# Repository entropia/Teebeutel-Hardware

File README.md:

# Teebeutel

An (experimental) ESP32-dev-board in the shape of the Entropia logo.

Head over to the [wiki](https://gitlab.jadyn.dev/jadyn/Teebeutel/-/wikis/home) for more information.

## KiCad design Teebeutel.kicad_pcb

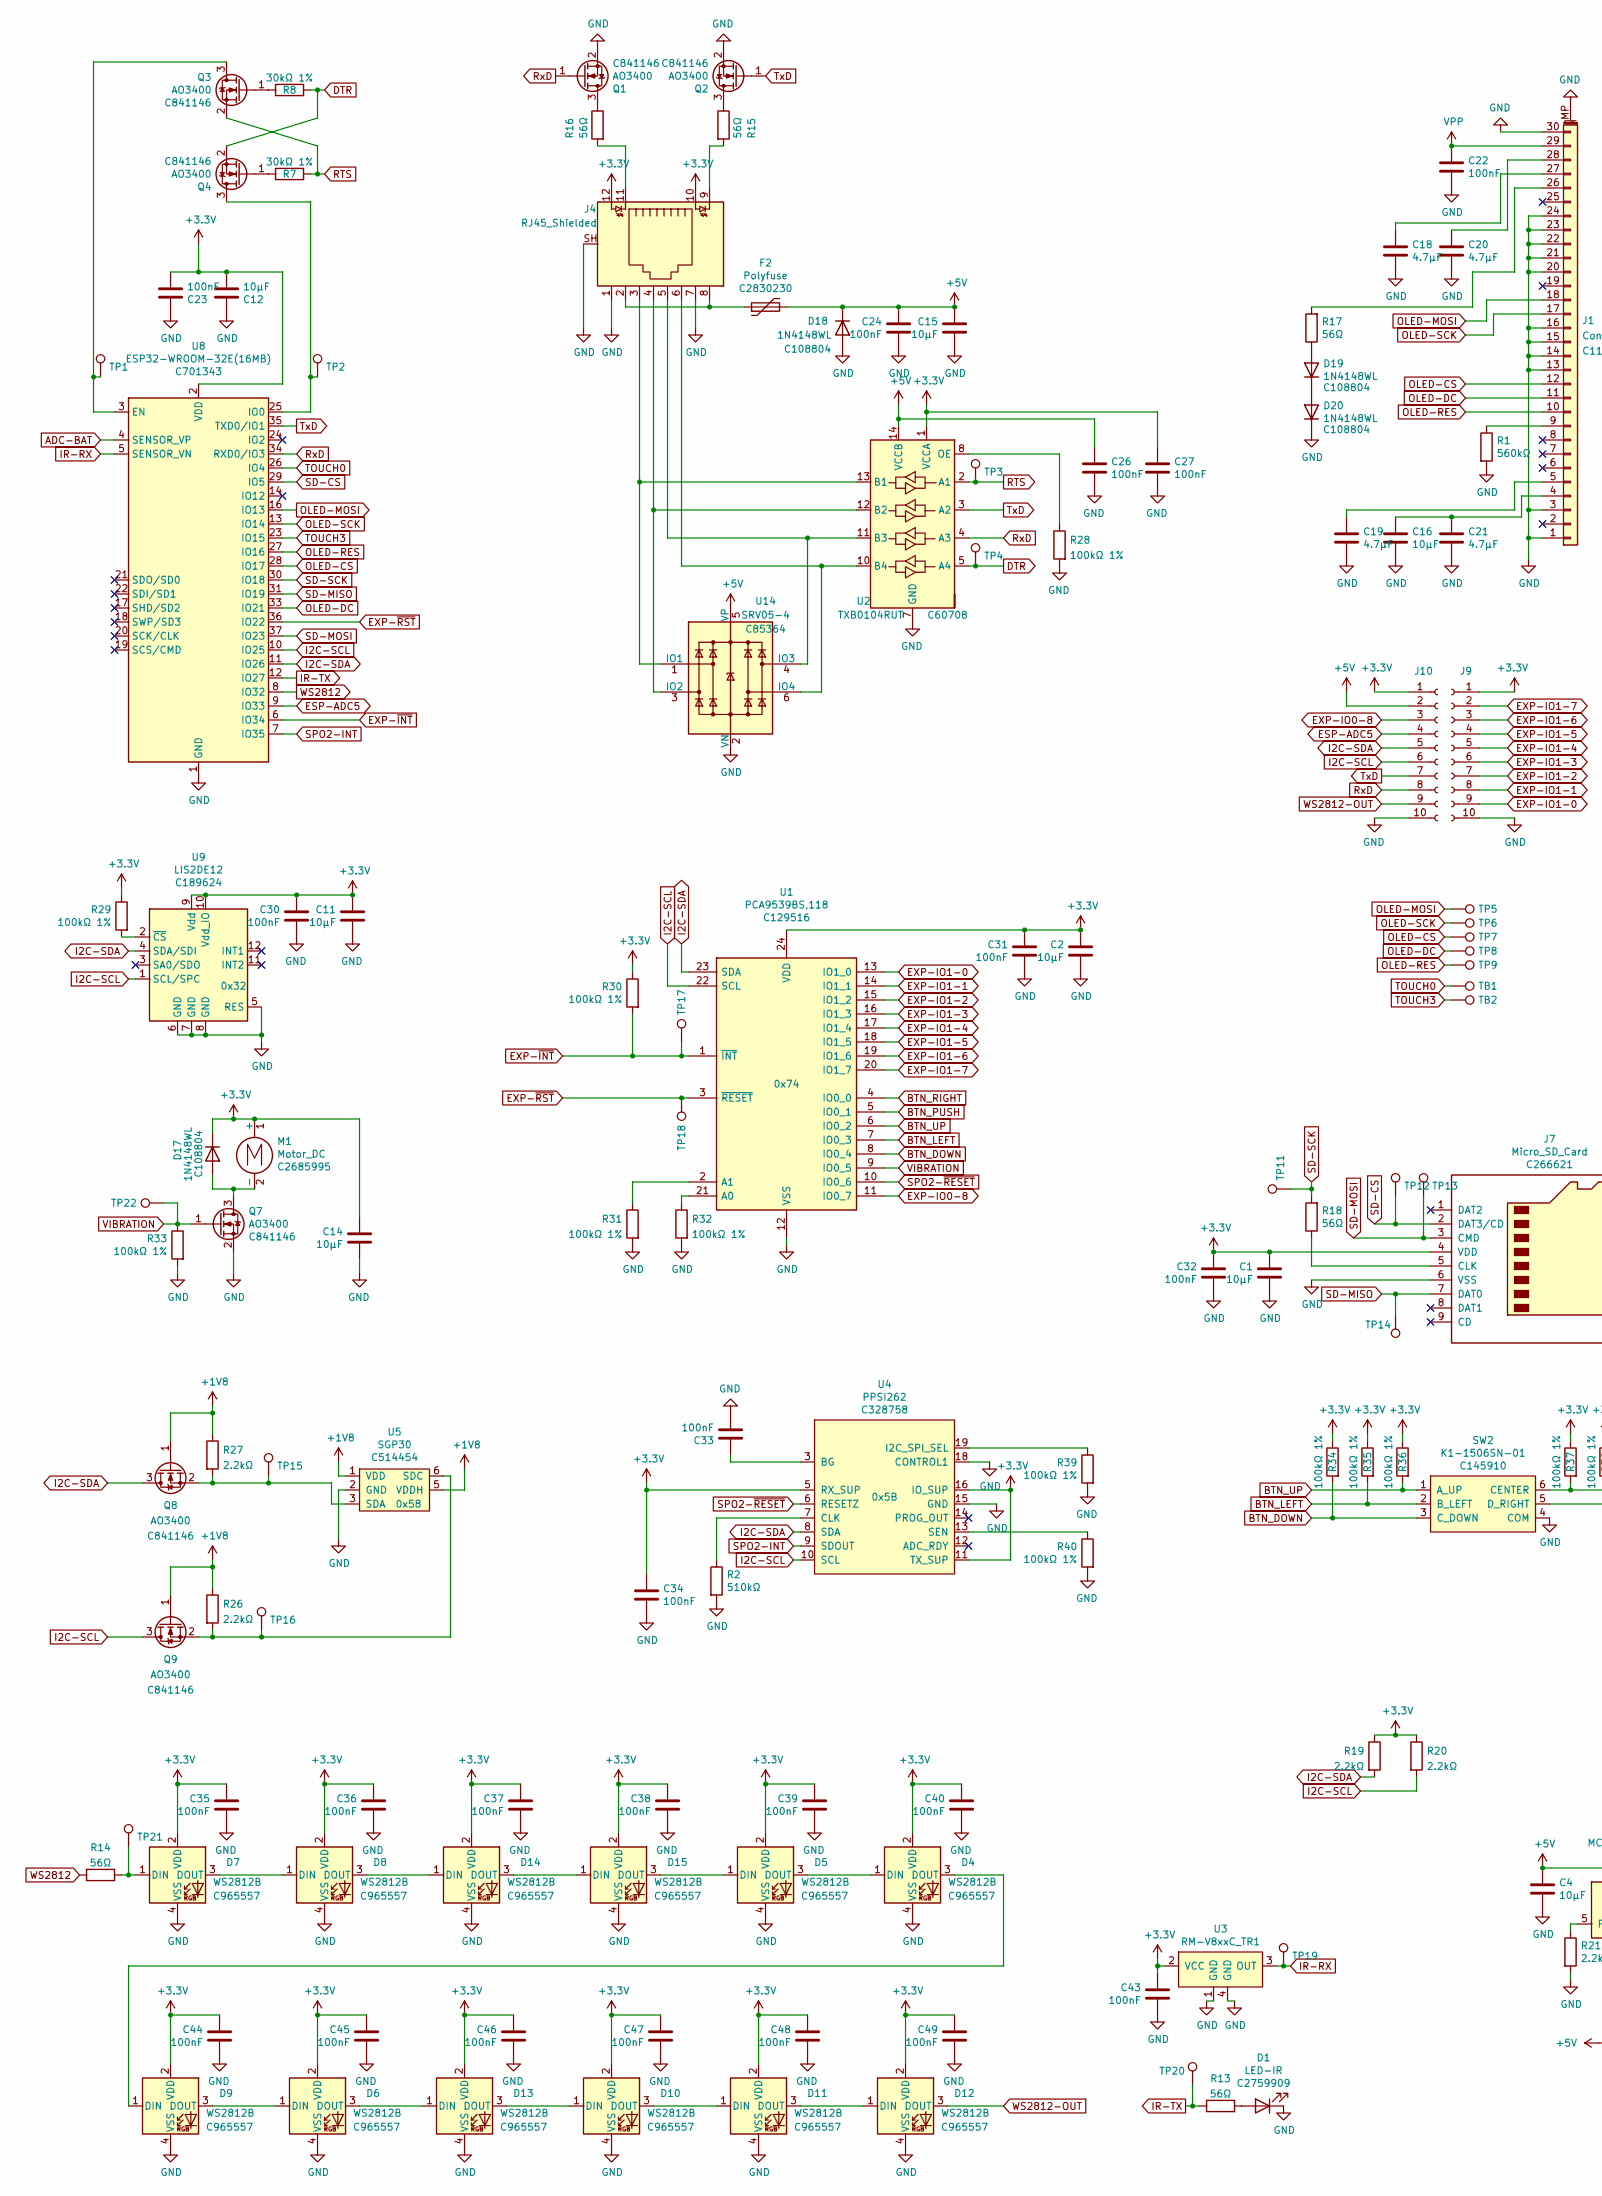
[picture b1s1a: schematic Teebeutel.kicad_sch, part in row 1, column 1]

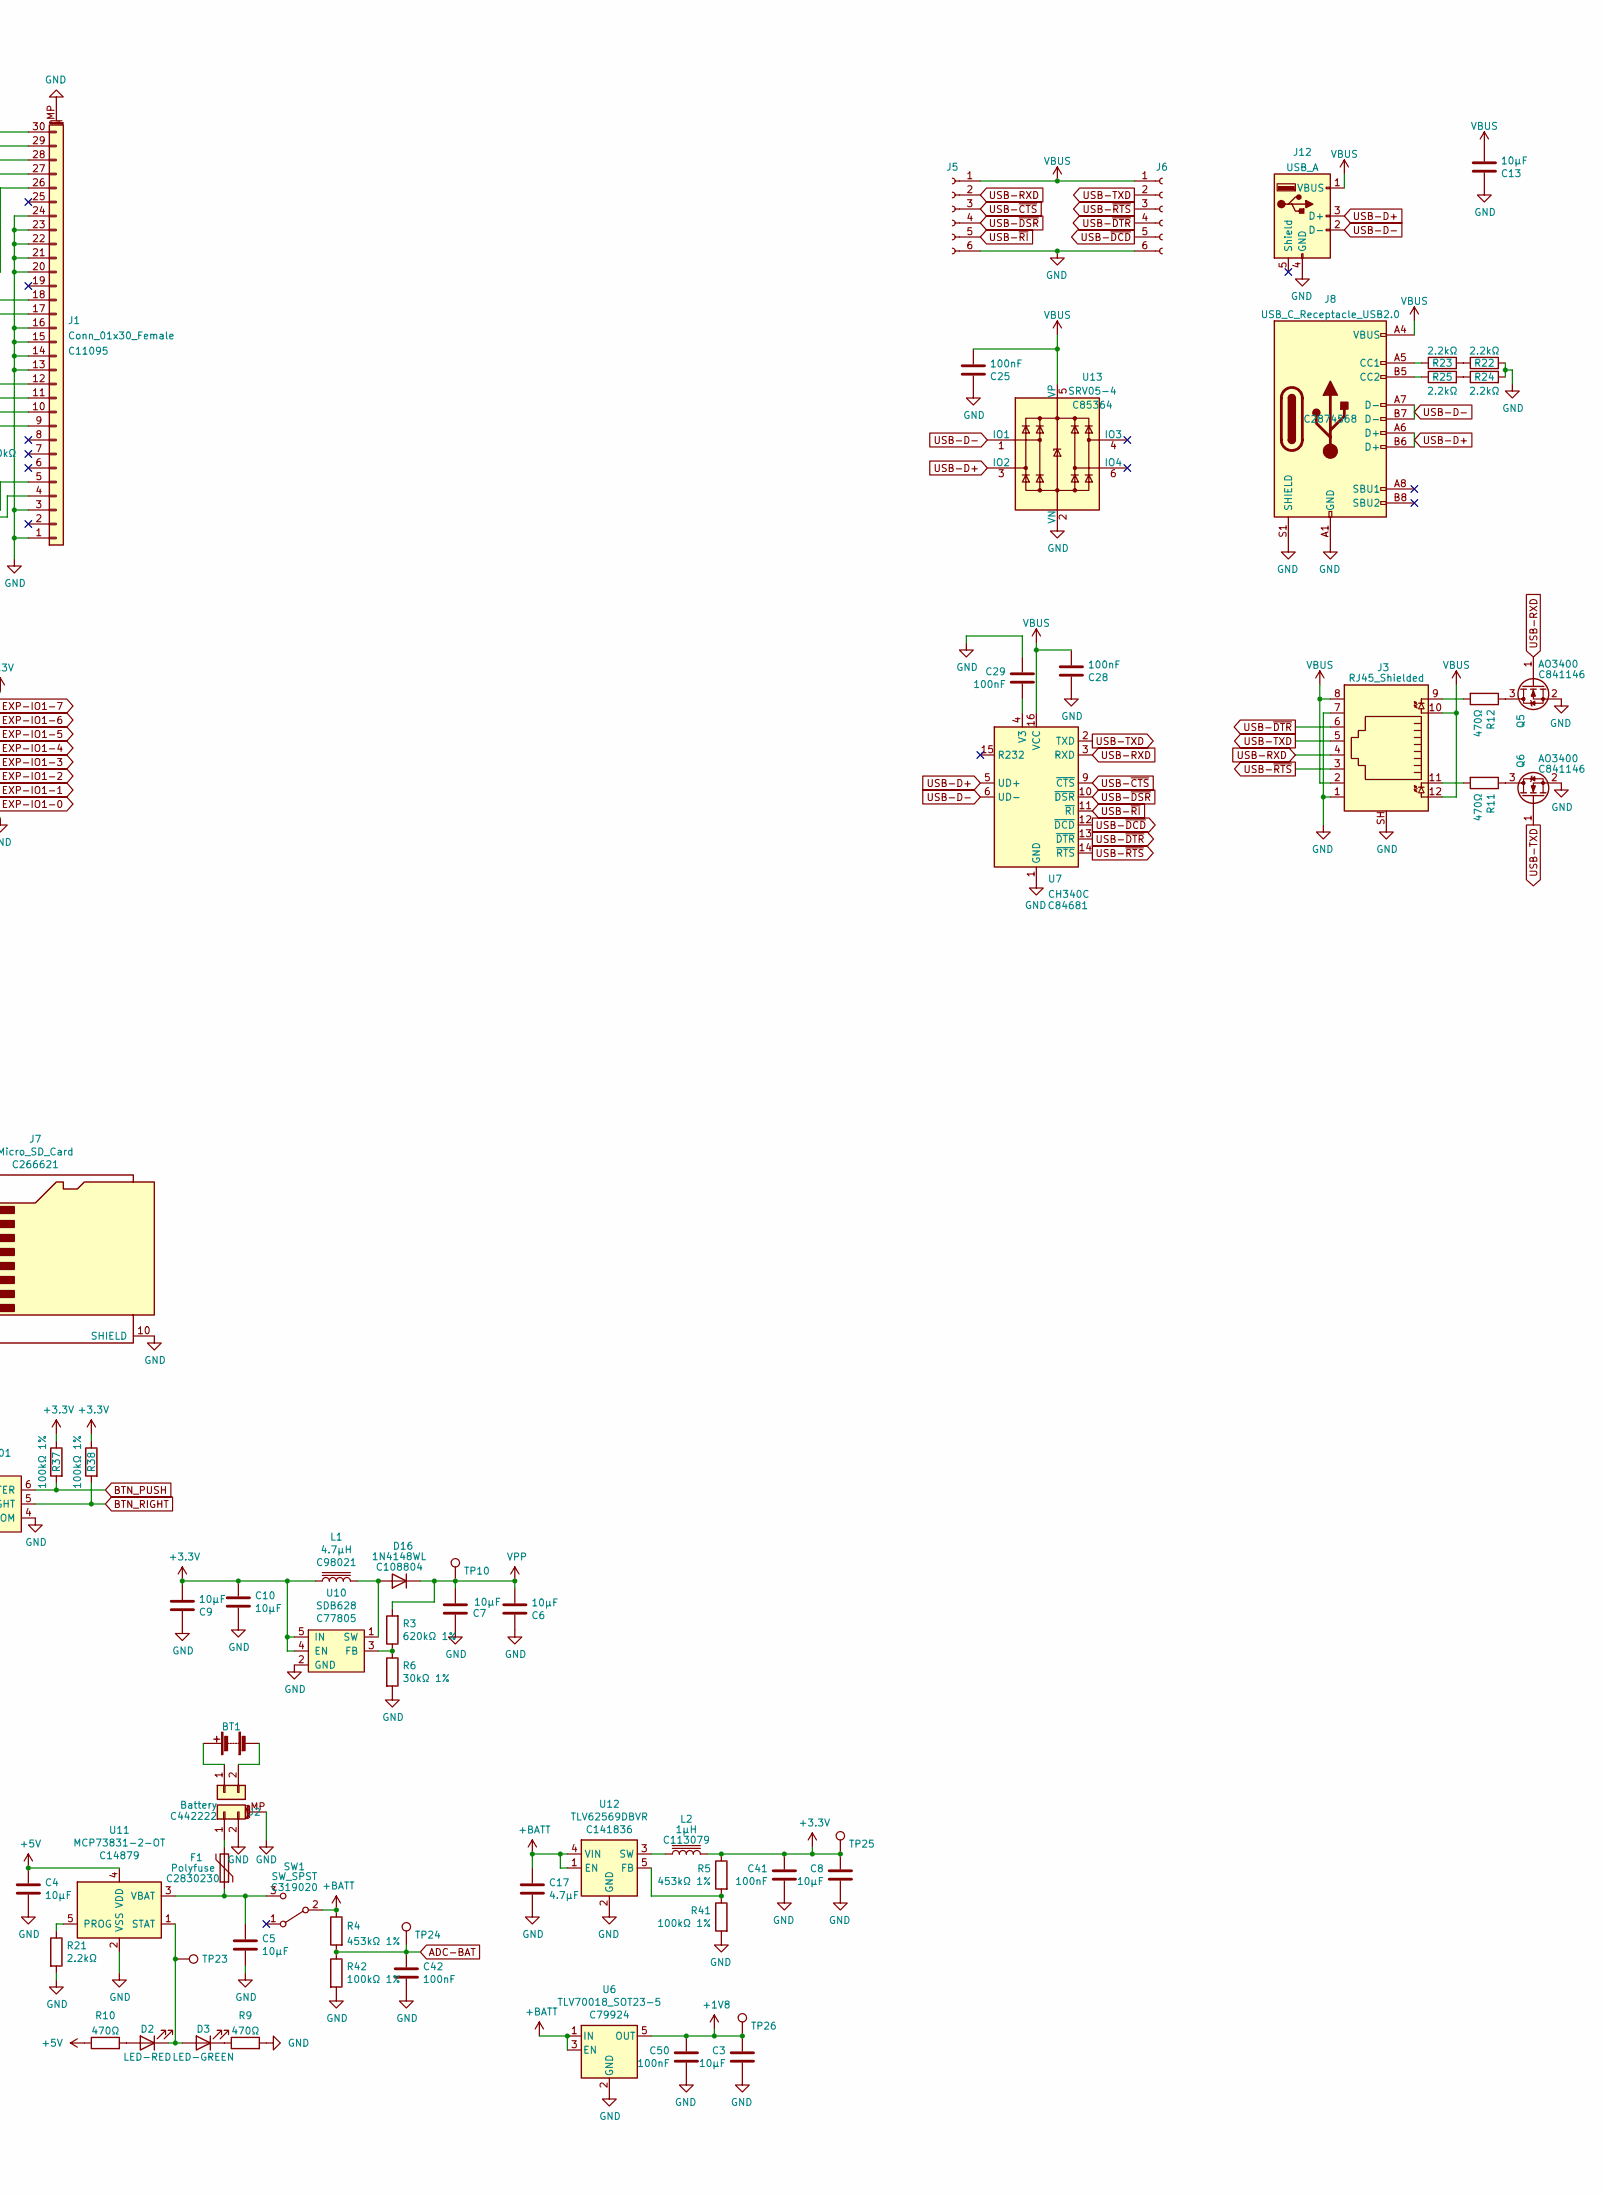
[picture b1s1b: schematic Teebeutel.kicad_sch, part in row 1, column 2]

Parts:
BT1: Battery
C1, C2, C3, C4, C5, C6, C7, C8, C9, C10, C11, C12, C13, C14, C15, C16: 10µF; C_0603_1608Metric; LCSC C19702
C17, C18, C19, C20, C21: 4.7µF; C_0603_1608Metric; LCSC C19666
C22, C23, C24, C25, C26, C27, C28, C29, C30, C31, C32, C33, C34, C35, C36, C37, C38, C39, C40, C41, C42, C43, C44, C45, C46, C47, C48, C49, C50: 100nF; C_0603_1608Metric; LCSC C14663
D1: LED-IR; LKIR30102C; LCSC C2759909
D2: LED-RED; LED_0805_2012Metric; LCSC C84256
D3: LED-GREEN; LED_0805_2012Metric; LCSC C84257
D4, D5, D6, D7, D8, D9, D10, D11, D12, D13, D14, D15: WS2812B; WS2812B-4020; LCSC C965557
D16, D17, D18, D19, D20: 1N4148WL; D_SOD-123F; LCSC C108804
F1, F2: Polyfuse; Fuse_0805_2012Metric; LCSC C2830230
J1: Conn_01x30_Female; TE_3-1734839-0_1x30-1MP_P0.5mm_Horizontal; LCSC C11095
J2: Battery; JST_PH_S2B-PH-SM4-TB_1x02-1MP_P2.00mm_Horizontal; LCSC C442222
J3, J4: RJ45_Shielded; RJ45_Amphenol_RJHSE538X; LCSC C464587
J5: Conn_01x06_Female; PinSocket_1x06_P2.54mm_Vertical_SMD_Pin1Right; MOUSER 801-83-006-30-001101
J6: Conn_01x06_Female; PinSocket_1x06_P2.54mm_Vertical_SMD_Pin1Left; MOUSER 801-83-006-30-001101
J7: Micro_SD_Card; TF15X15; LCSC C266621
J8: USB_C_Receptacle_USB2.0; USB_C_Receptacle_Palconn_UTC16-G; LCSC C2874568
J9: Conn_01x10_Female; PinSocket_1x10_P2.54mm_Vertical_SMD_Pin1Left; MOUSER 437-8018301030001101
J10: Conn_01x10_Female; PinSocket_1x10_P2.54mm_Vertical_SMD_Pin1Right; MOUSER 437-8018301030001101
J11: Battery
J12: USB_A; on-pcb-USB-A-Alignment-Holes
L1: 4.7µH; L_1210_3225Metric; LCSC C98021
L2: 1µH; L_1210_3225Metric; LCSC C113079
M1: Motor_DC; LNLON-S3070P; LCSC C2685995
Q1, Q2, Q3, Q4, Q5, Q6, Q7, Q8, Q9: AO3400; SOT-23; LCSC C841146
R1: 560kΩ; R_0603_1608Metric; LCSC C23203
R2: 510kΩ; R_0603_1608Metric; LCSC C23192
R3: 620kΩ 1%; R_0603_1608Metric; LCSC C23219
R4, R5: 453kΩ 1%; R_0603_1608Metric; LCSC C25818
R6, R7, R8: 30kΩ 1%; R_0603_1608Metric; LCSC C22984
R9, R10, R11, R12: 470Ω; R_0603_1608Metric; LCSC C116694
R13, R14, R15, R16, R17, R18: 56Ω; R_0603_1608Metric; LCSC C25196
R19, R20, R21, R22, R23, R24, R25, R26, R27: 2.2kΩ; R_0603_1608Metric; LCSC C113303
R28, R29, R30, R31, R32, R33, R34, R35, R36, R37, R38, R39, R40, R41, R42: 100kΩ 1%; R_0603_1608Metric; LCSC C25803
SW1: SW_SPST; SW_SPDT_PCM12; LCSC C319020
SW2: K1-1506SN-01; LCSC C145910
TB1: Touch Button 1; Touch-Button_Python
TB2: Touch Button 2; Touch-Button_OSHW
TP1: ESP32 EN; TestPoint_Pad_D1.0mm
TP2: ESP32 IO0; TestPoint_Pad_D1.0mm
TP3: DTR 3.3V; TestPoint_Pad_D1.0mm
TP4: RTS 3.3V; TestPoint_Pad_D1.0mm
TP5: OLED MOSI; TestPoint_Pad_D1.0mm
TP6: OLED SCK; TestPoint_Pad_D1.0mm
TP7: OLED CS; TestPoint_Pad_D1.0mm
TP8: OLED DC; TestPoint_Pad_D1.0mm
TP9: OLED RESET; TestPoint_Pad_D1.0mm
TP10: OLED VPP (13V); TestPoint_Pad_D1.0mm
TP11: SD-Card SCK; TestPoint_Pad_D1.0mm
TP12: SD-Card CS; TestPoint_Pad_D1.0mm
TP13: SD-Card MOSI; TestPoint_Pad_D1.0mm
TP14: SD-Card MISO; TestPoint_Pad_D1.0mm
TP15: I²C SDA 1.8V; TestPoint_Pad_D1.0mm
TP16: I²C SCL 1.8V; TestPoint_Pad_D1.0mm
TP17: EXP-INT; TestPoint_Pad_D1.0mm
TP18: EXP-~RST; TestPoint_Pad_D1.0mm
TP19: IR-RX; TestPoint_Pad_D1.0mm
TP20: IR-TX; TestPoint_Pad_D1.0mm
TP21: WS2821; TestPoint_Pad_D1.0mm
TP22: VIBRATION; TestPoint_Pad_D1.0mm
TP23: Charging status; TestPoint_Pad_D1.0mm
TP24: ADC Battery (1/4 Battery voltage); TestPoint_Pad_D1.0mm
TP25: V +3.3V; TestPoint_Pad_D1.0mm
TP26: V +1.8V; TestPoint_Pad_D1.0mm
U1: PCA9539BS,118; TSSOP-24_4.4x7.8mm_P0.65mm; LCSC C129516
U2: TXB0104RUT; TSSOP-14_4.4x5mm_P0.65mm; LCSC C60708
U3: RM-V8xxC_TR1; IRM-V8xxC-TR1; LCSC C264267
U4: PPSI262; LCSC C328758
U5: SGP30; LCSC C514454
U6: TLV70018_SOT23-5; SOT-23-5; LCSC C79924
U7: CH340C; SOIC-16_3.9x9.9mm_P1.27mm; LCSC C84681
U8: ESP32-WROOM-32E(16MB); ESP32-WROOM-32; LCSC C701343
U9: LIS2DE12; LGA-12_2x2mm_P0.5mm; LCSC C189624
U10: SDB628; SOT-23-6; LCSC C77805
U11: MCP73831-2-OT; SOT-23-5; LCSC C14879
U12: TLV62569DBVR; SOT-23-5; LCSC C141836
U13, U14: SRV05-4; SOT-23-6; LCSC C85364

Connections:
+1V8: C3.1, C50.1, Q8.1 (G), Q9.1 (G), R26.1, R27.1, TP26.1, U5.1 (VDD), U5.5 (VDDH), U6.5 (OUT)
+3V3: C1.1, C2.1, C8.1, C9.2, C10.1, C11.1, C12.2, C14.1, C23.2, C27.1, C30.1, C31.1, C32.1, C34.1, C35.1, C36.1, C37.1, C38.1, C39.1, C40.1, C41.1, C43.1, C44.1, C45.1, C46.1, C47.1, C48.1, C49.1, D4.2 (VDD), D5.2 (VDD), D6.2 (VDD), D7.2 (VDD), D8.2 (VDD), D9.2 (VDD), D10.2 (VDD), D11.2 (VDD), D12.2 (VDD), D13.2 (VDD), D14.2 (VDD), D15.2 (VDD), D17.1 (K), J4.10, J4.12, J7.4 (VDD), J9.1, J10.1, L1.1, L2.2, M1.1 (+), R5.1, R19.1, R20.1, R29.1, R30.1, R34.1, R35.1, R36.1, R37.1, R38.1, TP25.1, U1.24 (VDD), U2.1 (VCCA), U3.2 (VCC), U4.5 (RX_SUP), U4.11 (TX_SUP), U4.16 (IO_SUP), U8.2 (VDD), U9.9 (Vdd), U9.10 (Vdd_IO), U10.4 (EN), U10.5 (IN)
+5V: C4.1, C15.1, C24.1, C26.1, D18.1 (K), F2.2, J10.2, R10.1, U2.14 (VCCB), U11.4 (VDD), U14.5 (VP)
+BATT: C17.1, R4.1, SW1.2 (B), U6.1 (IN), U6.3 (EN), U12.1 (EN), U12.4 (VIN)
ADC-BAT: C42.1, R4.2, R42.1, TP24.1, U8.4 (SENSOR_VP)
BTN_DOWN: R34.2, SW2.3 (C_DOWN), U1.8 (IO0_4)
BTN_LEFT: R35.2, SW2.2 (B_LEFT), U1.7 (IO0_3)
BTN_PUSH: R37.2, SW2.6 (CENTER), U1.5 (IO0_1)
BTN_RIGHT: R38.2, SW2.5 (D_RIGHT), U1.4 (IO0_0)
BTN_UP: R36.2, SW2.1 (A_UP), U1.6 (IO0_2)
DTR: Q4.2 (S), R8.2, TP4.1, U2.5 (A4)
ESP-ADC5: J10.4, U8.9 (IO33)
EXP-IO0-8: J10.3, U1.11 (IO0_7)
EXP-IO1-0: J9.9, U1.13 (IO1_0)
EXP-IO1-1: J9.8, U1.14 (IO1_1)
EXP-IO1-2: J9.7, U1.15 (IO1_2)
EXP-IO1-3: J9.6, U1.16 (IO1_3)
EXP-IO1-4: J9.5, U1.17 (IO1_4)
EXP-IO1-5: J9.4, U1.18 (IO1_5)
EXP-IO1-6: J9.3, U1.19 (IO1_6)
EXP-IO1-7: J9.2, U1.20 (IO1_7)
EXP-~INT: R30.2, TP17.1, U1.1 (~INT), U8.6 (IO34)
EXP-~RST: TP18.1, U1.3 (~RESET), U8.36 (IO22)
GND: C1.2, C2.2, C3.2, C4.2, C5.2, C6.1, C7.2, C8.2, C9.1, C10.2, C11.2, C12.1, C13.1, C14.2, C15.2, C16.2, C17.2, C18.2, C19.2, C20.2, C21.2, C22.2, C23.1, C24.2, C25.1, C26.2, C27.2, C28.1, C29.1, C30.2, C31.2, C32.2, C33.2, C34.2, C35.2, C36.2, C37.2, C38.2, C39.2, C40.2, C41.2, C42.2, C43.2, C44.2, C45.2, C46.2, C47.2, C48.2, C49.2, C50.2, D1.1 (K), D4.4 (VSS), D5.4 (VSS), D6.4 (VSS), D7.4 (VSS), D8.4 (VSS), D9.4 (VSS), D10.4 (VSS), D11.4 (VSS), D12.4 (VSS), D13.4 (VSS), D14.4 (VSS), D15.4 (VSS), D18.2 (A), D20.1 (K), J1.1, J1.3, J1.13, J1.14, J1.15, J1.16, J1.20, J1.21, J1.22, J1.23, J1.24, J1.30, J1.MP (MountPin), J2.2, J2.MP (MountPin), J3.1, J3.7, J3.SH, J4.1, J4.7, J4.SH, J5.6, J6.6, J7.6 (VSS), J7.10 (SHIELD), J8.A1 (GND), J8.A12 (GND), J8.B1 (GND), J8.B12 (GND), J8.S1 (SHIELD), J9.10, J10.10, J12.4 (GND), Q1.2 (S), Q2.2 (S), Q5.2 (S), Q6.2 (S), Q7.2 (S), R1.2, R2.2, R6.2, R9.2, R21.2, R22.2, R24.2, R28.2, R31.2, R32.2, R33.2, R39.2, R40.2, R41.2, R42.2, SW2.4 (COM), U1.12 (VSS), U2.7 (GND), U3.1 (GND), U3.4 (GND), U4.15 (GND), U4.18 (CONTROL1), U5.2 (GND), U6.2 (GND), U7.1 (GND), U8.1 (GND), U8.15 (GND), U8.38 (GND), U8.39 (GND), U9.5 (RES), U9.6 (GND), U9.7 (GND), U9.8 (GND), U10.2 (GND), U11.2 (VSS), U12.2 (GND), U13.2 (VN), U14.2 (VN)
I2C-SCL: J10.6, Q9.3 (D), R20.2, U1.22 (SCL), U4.10 (SCL), U8.10 (IO25), U9.1 (SCL/SPC)
I2C-SDA: J10.5, Q8.3 (D), R19.2, U1.23 (SDA), U4.8 (SDA), U8.11 (IO26), U9.4 (SDA/SDI)
IR-RX: TP19.1, U3.3 (OUT), U8.5 (SENSOR_VN)
IR-TX: R13.1, TP20.1, U8.12 (IO27)
unnamed: BT1.1 (+), J11.1
unnamed: BT1.2 (-), J11.2
unnamed: C5.1, F1.1, SW1.3 (C), U11.3 (VBAT)
unnamed: C16.1, C21.1, J1.4
unnamed: C18.1, J1.27
unnamed: C19.1, J1.5
unnamed: C20.1, J1.28
unnamed: C29.2, U7.4 (V3)
unnamed: C33.1, U4.3 (BG)
unnamed: D1.2 (A), R13.2
unnamed: D2.1 (K), D3.2 (A), TP23.1, U11.1 (STAT)
unnamed: D2.2 (A), R10.2
unnamed: D3.1 (K), R9.1
unnamed: D4.1 (DIN), D5.3 (DOUT)
unnamed: D4.3 (DOUT), D9.1 (DIN)
unnamed: D6.1 (DIN), D9.3 (DOUT)
unnamed: D7.1 (DIN), R14.1, TP21.1
unnamed: D7.3 (DOUT), D8.1 (DIN)
unnamed: D10.1 (DIN), D13.3 (DOUT)
unnamed: D10.3 (DOUT), D11.1 (DIN)
unnamed: D11.3 (DOUT), D12.1 (DIN)
unnamed: D6.3 (DOUT), D13.1 (DIN)
unnamed: D8.3 (DOUT), D14.1 (DIN)
unnamed: D14.3 (DOUT), D15.1 (DIN)
unnamed: D5.1 (DIN), D15.3 (DOUT)
unnamed: D16.2 (A), L1.2, U10.1 (SW)
unnamed: D17.2 (A), M1.2 (-), Q7.3 (D)
unnamed: D19.1 (K), D20.2 (A)
unnamed: D19.2 (A), R17.1
unnamed: F1.2, J2.1
unnamed: F2.1, J4.2, J4.8
unnamed: J1.9, R1.1
unnamed: J1.26, R17.2
unnamed: J3.9, R12.2
unnamed: J3.11, R11.2
unnamed: J4.3, U2.13 (B1), U14.1 (IO1)
unnamed: J4.4, U2.12 (B2), U14.3 (IO2)
unnamed: J4.5, U2.11 (B3), U14.4 (IO3)
unnamed: J4.6, U2.10 (B4), U14.6 (IO4)
unnamed: J4.9, R15.2
unnamed: J4.11, R16.2
unnamed: J7.5 (CLK), R18.1
unnamed: J8.A5 (CC1), R23.1
unnamed: J8.B5 (CC2), R25.1
unnamed: L2.1, U12.3 (SW)
unnamed: Q1.3 (D), R16.1
unnamed: Q2.3 (D), R15.1
unnamed: Q3.1 (G), R8.1
unnamed: Q3.3 (D), TP1.1, U8.3 (EN)
unnamed: Q4.1 (G), R7.1
unnamed: Q4.3 (D), TP2.1, U8.25 (IO0)
unnamed: Q5.3 (D), R12.1
unnamed: Q6.3 (D), R11.1
unnamed: Q8.2 (S), R27.2, TP15.1, U5.3 (SDA)
unnamed: Q9.2 (S), R26.2, TP16.1, U5.6 (SDC)
unnamed: R2.1, U4.7 (CLK)
unnamed: R3.1, R6.1, U10.3 (FB)
unnamed: R21.1, U11.5 (PROG)
unnamed: R22.1, R23.2
unnamed: R24.1, R25.2
unnamed: R28.1, U2.8 (OE)
unnamed: R29.2, U9.2 (~CS)
unnamed: R31.1, U1.2 (A1)
unnamed: R32.1, U1.21 (A0)
unnamed: R39.1, U4.19 (I2C_SPI_SEL)
unnamed: R40.1, U4.13 (SEN)
unnamed: R5.2, R41.1, U12.5 (FB)
OLED-CS: J1.12, TP7.1, U8.28 (IO17)
OLED-DC: J1.11, TP8.1, U8.33 (IO21)
OLED-MOSI: J1.18, TP5.1, U8.16 (IO13)
OLED-RES: J1.10, TP9.1, U8.27 (IO16)
OLED-SCK: J1.17, TP6.1, U8.13 (IO14)
RTS: Q3.2 (S), R7.2, TP3.1, U2.2 (A1)
RxD: J10.8, Q1.1 (G), U2.4 (A3), U8.34 (RXD0/IO3)
SD-CS: J7.2 (DAT3/CD), TP12.1, U8.29 (IO5)
SD-MISO: J7.7 (DAT0), TP14.1, U8.31 (IO19)
SD-MOSI: J7.3 (CMD), TP13.1, U8.37 (IO23)
SD-SCK: R18.2, TP11.1, U8.30 (IO18)
SPO2-INT: U4.9 (SDOUT), U8.7 (IO35)
SPO2-~RESET: U1.10 (IO0_6), U4.6 (RESETZ)
TOUCH0: TB1.1, U8.26 (IO4)
TOUCH3: TB2.1, U8.23 (IO15)
TxD: J10.7, Q2.1 (G), U2.3 (A2), U8.35 (TXD0/IO1)
USB-D+: J8.A6 (D+), J8.B6 (D+), J12.3 (D+), U7.5 (UD+), U13.3 (IO2)
USB-D-: J8.A7 (D-), J8.B7 (D-), J12.2 (D-), U7.6 (UD-), U13.1 (IO1)
USB-RXD: J3.4, J5.2, Q5.1 (G), U7.3 (RXD)
USB-TXD: J3.5, J6.2, Q6.1 (G), U7.2 (TXD)
USB-~CTS: J5.3, U7.9 (~CTS)
USB-~DCD: J6.5, U7.12 (~DCD)
USB-~DSR: J5.4, U7.10 (~DSR)
USB-~DTR: J3.6, J6.4, U7.13 (~DTR)
USB-~RI: J5.5, U7.11 (~RI)
USB-~RTS: J3.3, J6.3, U7.14 (~RTS)
VBUS: C13.2, C25.2, C28.2, J3.2, J3.8, J3.10, J3.12, J5.1, J6.1, J8.A4 (VBUS), J8.A9 (VBUS), J8.B4 (VBUS), J8.B9 (VBUS), J12.1 (VBUS), U7.16 (VCC), U13.5 (VP)
VIBRATION: Q7.1 (G), R33.1, TP22.1, U1.9 (IO0_5)
VPP: C6.2, C7.1, C22.1, D16.1 (K), J1.29, R3.2, TP10.1
WS2812: R14.2, U8.8 (IO32)
WS2812-OUT: D12.3 (DOUT), J10.9

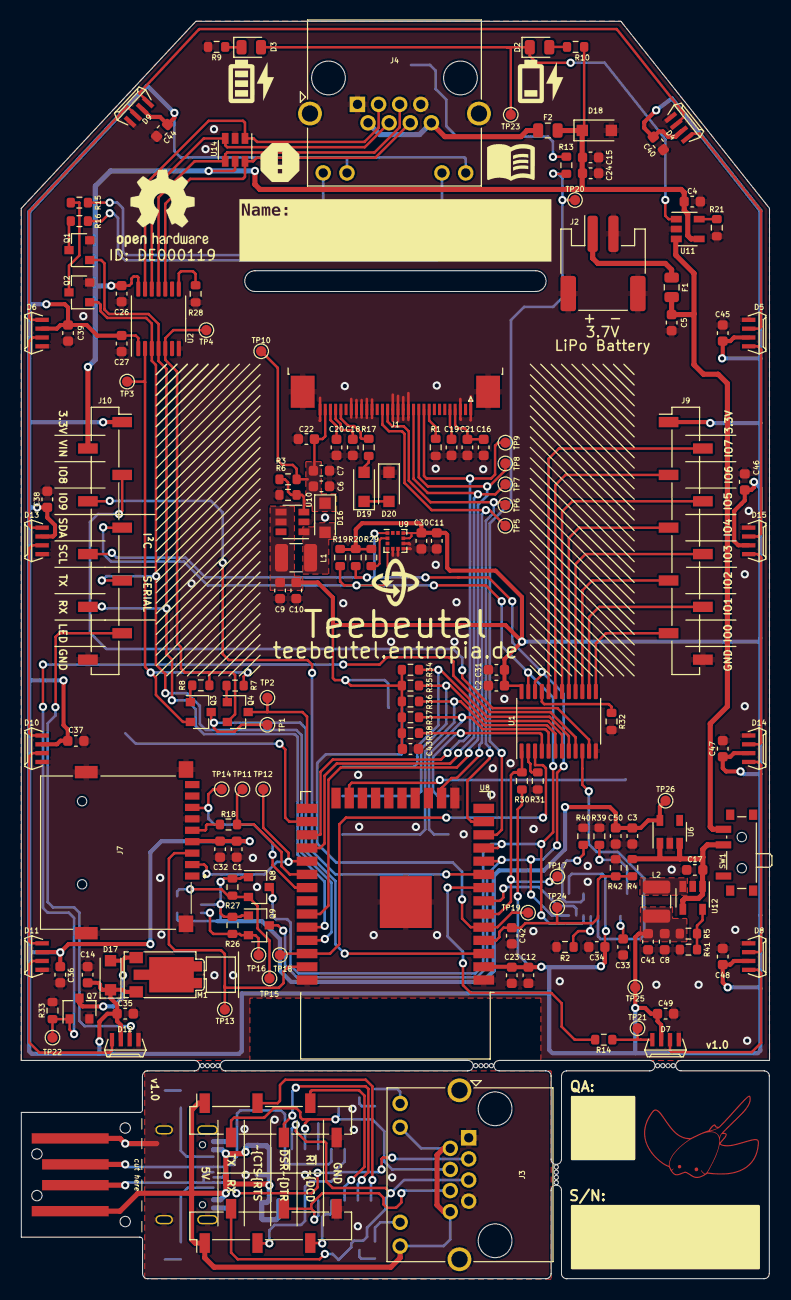
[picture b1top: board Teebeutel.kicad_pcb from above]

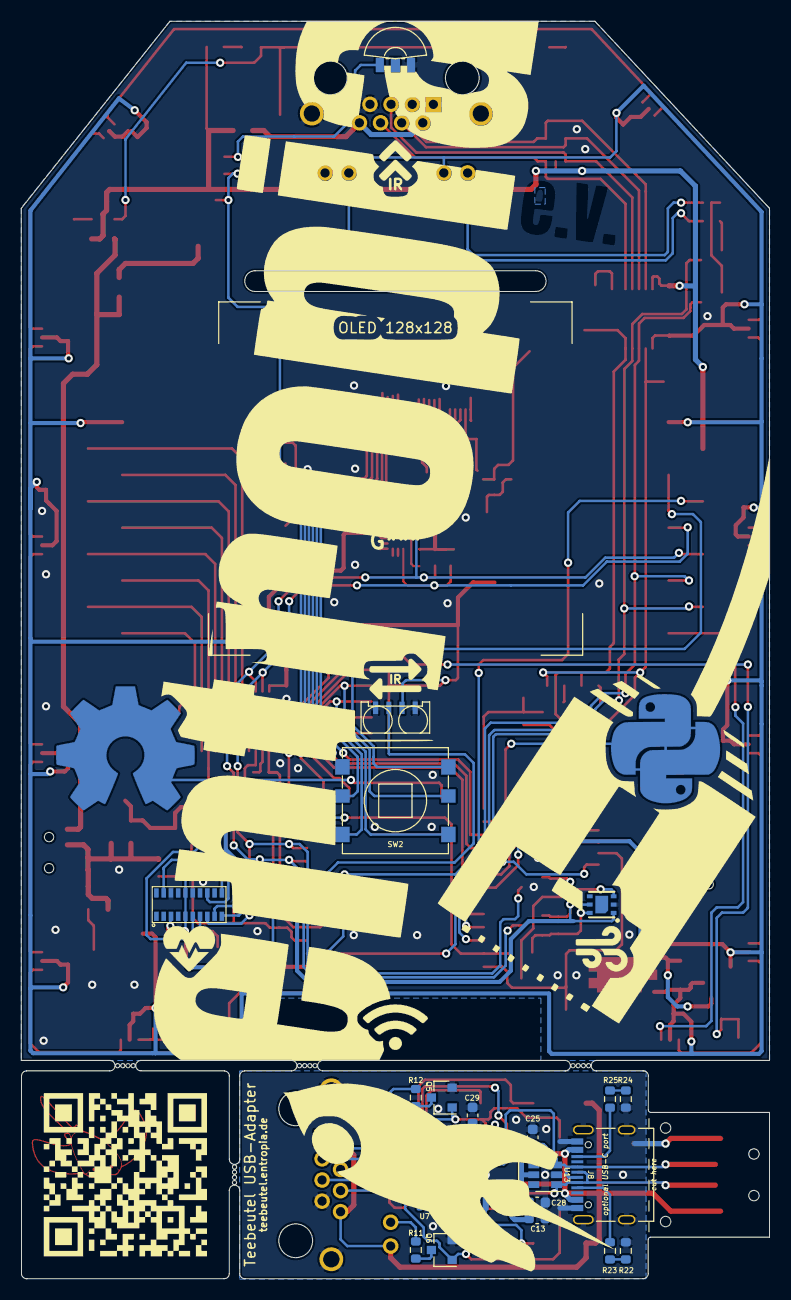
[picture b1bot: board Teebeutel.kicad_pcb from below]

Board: 2 copper layers, 72.0 x 121.0 mm, 181 parts (22 on the bottom side), 124 nets.

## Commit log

2021-11-04 feat: add SD-Card, accelerometer and SDI for display
2021-11-04 feat: add chargin indicators and touch inputs
2021-11-04 feat: add ws2812 leds
2021-11-04 feat: add MORE sensors
2021-11-04 feat: add SD-Card footprint and some cleanup
2021-11-04 fix: SD-Card 3D-Model Alignment
2021-11-05 fix: Move pulldown R in the Boot-mode selector
2021-11-05 feat: add buzzer
2021-11-05 feat: add llc for uart
2021-11-06 feat: alot of stuff and routing
2021-11-06 feat: alot of stuff
2021-11-06 feat(): Finished routing and some clean up
2021-11-06 feat(): finish routing and assigning JLCPCB part numbers
2021-11-07 feat(): add IR-Tranceiver and some 3D-Models
2021-11-07 feat(): all 3D-Models are in
2021-11-07 fix: rearanged some traces and vias for better GND planes
2021-11-07 feat: Update graphic
2021-11-07 feat: Update gerber files
2021-11-07 fix: Improve Vcc Trace
2021-11-08 fix: use the correct display connector
2021-11-10 feat(): Add graphics
2021-11-10 fix(): Small graphics glitches/scaling issues
2021-11-13 fix+cleanup: more cleanup and fixes, retouched all Cs
2021-11-13 feat: all License
2021-11-15 fix(D16, D17): Change part number
2021-11-15 feat(): Retouch placement of component labels
2021-11-16 feat(): Add 100nF and 10µF to ESP32-VCC
2021-11-16 chore: Cleanup some files
2021-11-16 chore: Update README
2021-11-16 docs(): Add 3D renders
2021-11-16 fix: Change to available LSCS-Parts
2021-11-16 chore: Update GERBER
2021-11-17 doc(D11, D19): Add datasheet
2021-11-18 feat(): add Cs to SD-Card Vcc
2021-11-18 chore: update refs, bom, documentation
2021-11-19 feat(): Add name-tag, stencil tooling holes, OSHW-Information
2021-11-19 chore: generate gerber + drill files
2021-11-22 fix: Move stencil tooling holes to *.Mask layer
2021-12-01 chore(OSHWA): Add ID (DE000117)
2021-12-01 feat(ibom): add ibom
2021-12-05 fix(ESP): Rework the ESP connections.
2021-12-05 feat(): Started work on v1.0
2021-12-07 feat: Replace expensive IO-Expantion with cheaper IC
2021-12-09 Add vibration motor
2021-12-09 feat: more routing work
2021-12-12 feat: add I²C Addresses
2021-12-18 small changes
2021-12-20 docs: Initial commit
2021-12-20 refactor: clean up old files
2021-12-20 docs: Create first documentation and structure
2021-12-20 docs: add antora docs
2021-12-28 chore: Add CONTRIBUTING.md
2021-12-28 feat(): Change footprints
2021-12-28 docs: Add navigation
2021-12-29 chore: cleanup and update to KiCad6
2021-12-31 pcb: finish routing
2021-12-31 chore: Update version numbers and urls
2022-01-03 fix: rework footprint
2022-01-03 Schematic: Lowered I2C pullup to 2.2k, exchanged I2C level shifter, changed FFC to mounting-pin version, fixed PPSI262 pinout
2022-01-03 Layout: Routed new PPSI262 layout, added cutout zones for narrow parts, routed new I2C level shifter
2022-01-03 feat(): Connect ~RESET from PPSI to IO-Exp
2022-01-03 chore: update docs
2022-01-05 refactor: remove bluetooth icon
2022-01-05 feat(sch): Switch DC-DC converter
2022-01-05 feat(esp): Upgrade to latest ESP32-WROOM with 16MB flash
2022-01-09 chore(OSHW): Update OSHW-ID
2022-01-12 feat(): Add USB-Adaptor
2022-01-12 typo: rename to fontawesome
2022-01-12 feat(icons): replace text with pictograms
2022-01-12 Schematic: Added capacitors to CH340C
2022-01-18 feat(): Add fuse and finalize USB-Adaptor
2022-01-18 feat(): Add fairydust
2022-01-20 schematic: removed C24
2022-01-20 schematic: removed 10k bom entry, replaced 10k with either 100k or 2.2k; fixed critical I2C level shifter error
2022-01-20 schematic: added Pulldown resistors to Type-C receptacle
2022-01-20 schematic: added 100nF to RM-V8xxC_TR1
2022-01-20 schematic: removed 82ohm BOM entry
2022-01-20 schematic: added 10ohm to WS2812 data
2022-01-20 schematic: replaced R21, reduced BOM count
2022-01-20 schematic: beautify labels
2022-01-20 schematic: added ESD protection to USB data lines
2022-01-20 schematic: moved J10 and U5 to correct grid
2022-01-20 schematic: annotated schematic
2022-01-21 rebase(): Delete unused file
2022-01-21 refactor(): Use bigger sheet and clean up
2022-01-21 feat(): Update pcb
2022-01-21 chore(): Update / Add partnumbers
2022-01-22 feat(): Place footprint references
2022-02-13 feat(): Reassinged refs, cleanup
2022-02-14 chore: Further clean up and BOM reduction
2022-02-18 chore(): Cleanup
2022-02-19 chore(): Cleanup BOM and update docs
2022-02-21 feat(pcb): Lot's of cleanup and rework
2022-02-23 workflow: Trigger documentation updates automatically
2022-02-23 docs: Extend docs
2022-02-24 feat(pcb): Add alternative logo, without the 'e.V.'
2022-02-24 feat(pcb): Add 'e.V.' as CU keepout area
2022-03-07 feat(pcb): Add more alternative logos
2022-03-07 chore(sch): Update partnumbers and names

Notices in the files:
Teebeutel.kicad_pcb:
License: CERN-OHL-S
